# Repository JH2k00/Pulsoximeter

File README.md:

# Pulsoximeter
Pulsoximeter Projekt für den ETV

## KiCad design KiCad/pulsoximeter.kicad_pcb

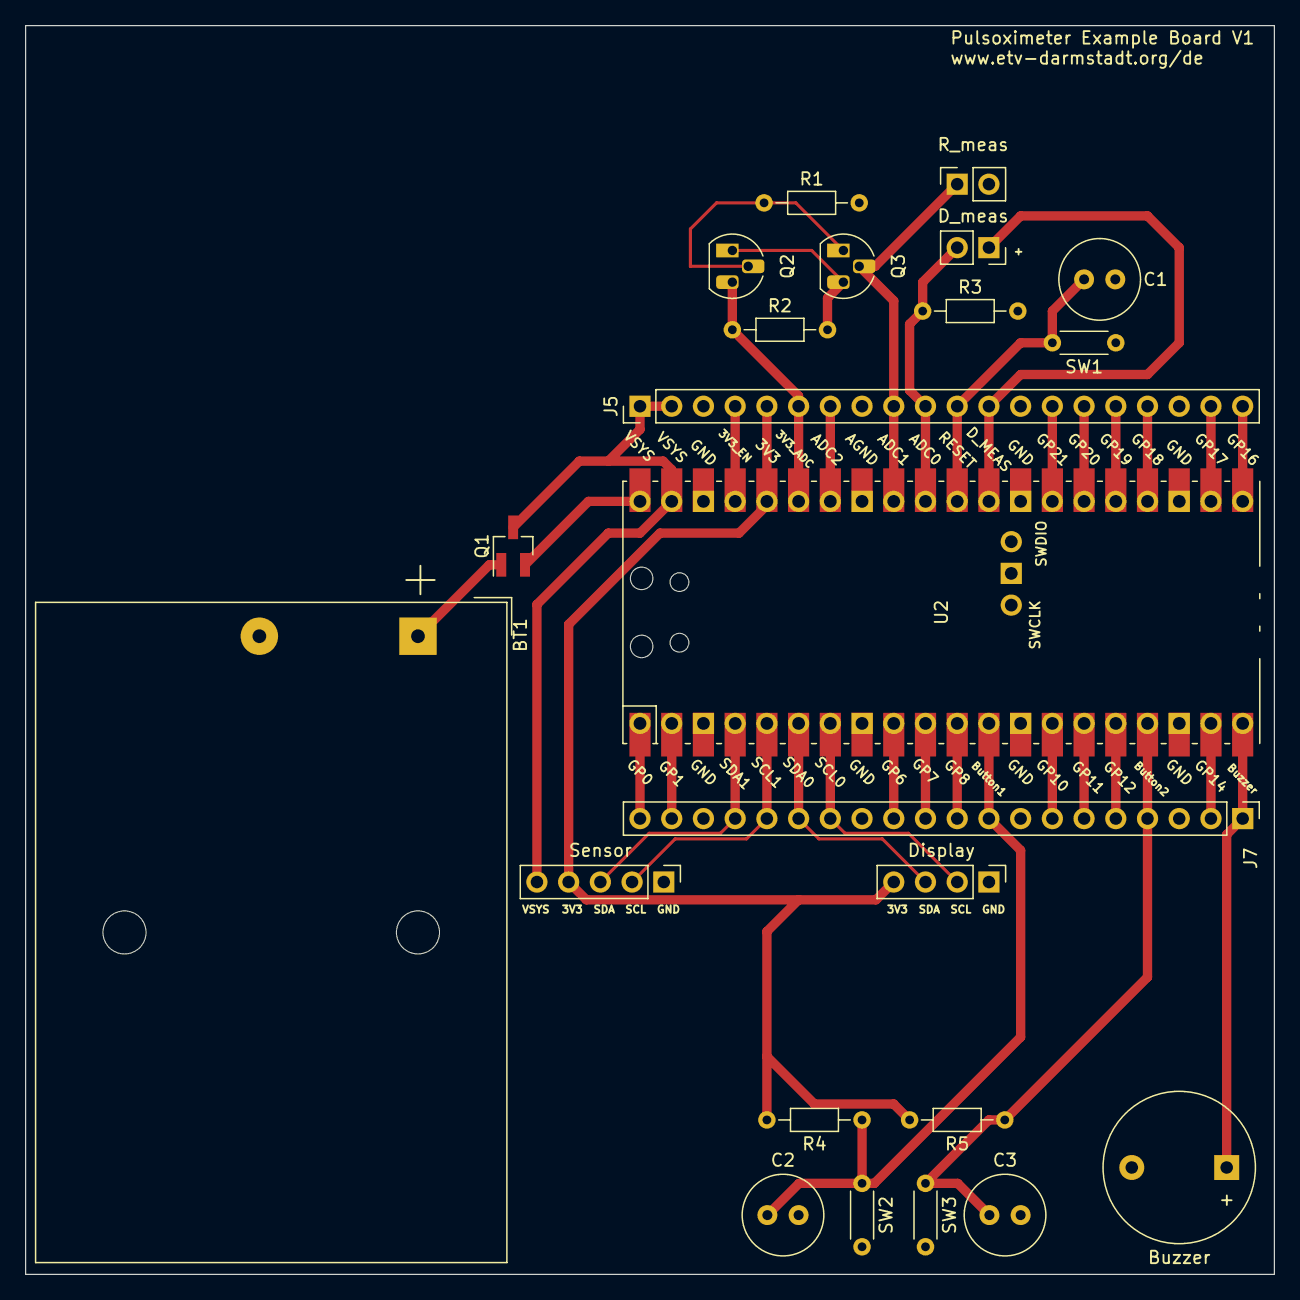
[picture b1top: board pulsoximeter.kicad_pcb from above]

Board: 2 copper layers, 100.0 x 100.0 mm, 23 parts (0 on the bottom side), 36 nets.

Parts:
BT1: Battery; BatteryHolder_Keystone_2479_3xAAA
Buzzer: Buzzer; Buzzer_12x9.5RM7.6
C1, C2, C3: 100n; C_Radial_D6.3mm_H5.0mm_P2.50mm
D_meas: D_meas; PinSocket_1x02_P2.54mm_Vertical
Display: Display Connector; PinHeader_1x04_P2.54mm_Vertical
J5: Analog; PinHeader_1x20_P2.54mm_Vertical
J7: Digital; PinHeader_1x20_P2.54mm_Vertical
Q1: DMG2305UX-13; SOT-23_Handsoldering
Q2, Q3: 2N3906C; TO-92_HandSolder
R1: 1Meg; R_Axial_DIN0204_L3.6mm_D1.6mm_P7.62mm_Horizontal
R2: 2k; R_Axial_DIN0204_L3.6mm_D1.6mm_P7.62mm_Horizontal
R3: 1k; R_Axial_DIN0204_L3.6mm_D1.6mm_P7.62mm_Horizontal
R4, R5: 10k; R_Axial_DIN0204_L3.6mm_D1.6mm_P7.62mm_Horizontal
R_meas: R_meas; PinSocket_1x02_P2.54mm_Vertical
SW1: SW_Push; R_Axial_DIN0204_L3.6mm_D1.6mm_P5.08mm_Horizontal
SW2: Display_Button; R_Axial_DIN0204_L3.6mm_D1.6mm_P5.08mm_Horizontal
SW3: Display_Button_2; R_Axial_DIN0204_L3.6mm_D1.6mm_P5.08mm_Horizontal
Sensor: MAX30102; PinHeader_1x05_P2.54mm_Vertical
U2: PicoW; RPi_PicoW_SMD_TH

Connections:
+3V3: Display.4, J5.5, R4.2, R5.2, Sensor.4, U2.36 (3V3)
+BATT: BT1.1 (+), Q1.1 (D)
/3V3_ADC: J5.6, Q2.3 (E), R2.1, U2.35 (ADC_VREF)
/3V3_EN: J5.4, U2.37 (3V3_EN)
/ADC0: D_meas.2, J5.10, R3.1, U2.31 (GPIO26_ADC0)
/ADC1: J5.9, Q3.2 (C), R_meas.1, U2.32 (GPIO27_ADC1)
/Buzzer: Buzzer.1 (-), J7.1, U2.20 (GPIO15)
/Diode_Meas: D_meas.1, J5.12, U2.29 (GPIO22)
/Display_Button1: C2.1, J7.9, R4.1, SW2.1, U2.12 (GPIO9)
/Display_Button2: C3.1, J7.4, R5.1, SW3.1, U2.17 (GPIO13)
/GP0: J7.20, U2.1 (GPIO0)
/GP1: J7.19, U2.2 (GPIO1)
/GP6: J7.12, U2.9 (GPIO6)
/GP7: J7.11, U2.10 (GPIO7)
/GP8: J7.10, U2.11 (GPIO8)
/GP10: J7.7, U2.14 (GPIO10)
/GP11: J7.6, U2.15 (GPIO11)
/GP12: J7.5, U2.16 (GPIO12)
/GP14: J7.2, U2.19 (GPIO14)
/GP16: J5.20, U2.21 (GPIO16)
/GP17: J5.19, U2.22 (GPIO17)
/GP18: J5.17, U2.24 (GPIO18)
/GP19: J5.16, U2.25 (GPIO19)
/GP20: J5.15, U2.26 (GPIO20)
/GP21: J5.14, U2.27 (GPIO21)
/GP28: J5.7, U2.34 (GPIO28_ADC2)
/I2C0 SCL: Display.2, J7.14, U2.7 (GPIO5)
/I2C0 SDA: Display.3, J7.15, U2.6 (GPIO4)
/I2C1 SCL: J7.16, Sensor.2, U2.5 (GPIO3)
/I2C1 SDA: J7.17, Sensor.3, U2.4 (GPIO2)
/RESET: C1.2, J5.11, SW1.2, U2.30 (RUN)
/VSYS: J5.1, J5.2, Q1.3 (S), Sensor.5, U2.39 (VSYS)
GND: BT1.2 (-), Buzzer.2 (+), C1.1, C2.2, C3.2, Display.1, J5.3, J5.8, J5.13, J5.18, J7.3, J7.8, J7.13, J7.18, R1.2, R3.2, R_meas.2, SW1.1, SW2.2, SW3.2, Sensor.1, U2.3 (GND), U2.8 (GND), U2.13 (GND), U2.18 (GND), U2.23 (GND), U2.28 (GND), U2.33 (AGND), U2.38 (GND)
unnamed: Q2.1 (B), Q3.3 (E), R2.2
unnamed: Q2.2 (C), Q3.1 (B), R1.1
VBUS: Q1.2 (G), U2.40 (VBUS)

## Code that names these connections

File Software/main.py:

from ulab import numpy as np
from machine import Pin, I2C, ADC, PWM
from MAX30102 import MAX30102, MAX3010X_I2C_ADDRESS, MAX30105_PULSEAMP_MEDIUM, MAX30105_PULSEAMP_LOW, I2C_SPEED_FAST, MAX30105_PULSEAMP_HIGH
import ssd1306
from utils import CONST_FIR_COEFFS
import struct
import asyncio
from utils import CONST_TONES, CONST_DEFAULT_SONG

from micropython import const

import aioble
import bluetooth

# org.bluetooth.service.pulse_oximeter
_PLX_SENSE_UUID = bluetooth.UUID(0x1822)

# org.bluetooth.characteristic.heart_rate_measurement
_PLX_CHAR_HR_UUID = bluetooth.UUID(0x2A37)

# org.bluetooth.characteristic.gap.appearance.xml
_ADV_APPEARANCE_GENERIC_PULSE_OXIMETER = const(0x0C40)

# How frequently to send advertising beacons.
_ADV_INTERVAL_MS = const(250000)

# Register GATT server.
plx_service = aioble.Service(_PLX_SENSE_UUID)
plx_characteristic = aioble.Characteristic(
    plx_service, _PLX_CHAR_HR_UUID, read=True, notify=True
)
aioble.register_services(plx_service)

I2C_0_SDA_PIN = Pin(4, pull=Pin.PULL_UP) # GPIO4 = Pin 6
I2C_0_SCL_PIN = Pin(5, pull=Pin.PULL_UP) # GPIO5 = Pin 7

I2C_1_SDA_PIN = Pin(2, pull=Pin.PULL_UP) # GPIO2 = Pin 4
I2C_1_SCL_PIN = Pin(3, pull=Pin.PULL_UP) # GPIO3 = Pin 5

adc1 = ADC(Pin(27, mode=Pin.IN))

gpio_pin = Pin(22, mode=Pin.OUT, value=1)
adc0 = ADC(Pin(26, mode=Pin.IN))

DISPLAY_STATE = 0 # 0 -> HR, 1-> Resistor, 2-> Diode

buzzer = PWM(Pin(15))
buzzer.freq(500)

def button_handler(pin):
    global DISPLAY_STATE
    DISPLAY_STATE = (DISPLAY_STATE + 1) % 3

button_2 = Pin(13, mode=Pin.IN)
button_2.irq(trigger=Pin.IRQ_FALLING, handler=button_handler)

I = 0.241751 # 0.241751 mA
U_LSB = (3.3) / (2**16) # U_ref = 3.3V, U_LSB = (U_ref / 2^n) V

LED = Pin('LED', Pin.OUT)
LED.toggle()

fs = 50 # Normal Heart rate is around 30-300 bpm -> f_max = 300 / 60 Hz = 5 Hz -> 50Hz sampling rate is more than enough

def i2c_print(devices):
        if len(devices) == 0:
            print("No i2c device !")
        else:
            print('i2c devices found:',len(devices))

        for device in devices:
            print("Decimal address: ",device," | Hexa address: ",hex(device))

i2c_0 = I2C(0, sda=I2C_0_SDA_PIN, scl=I2C_0_SCL_PIN, freq=I2C_SPEED_FAST)
i2c_print(devices=i2c_0.scan())

i2c_1 = I2C(1, sda=I2C_1_SDA_PIN, scl=I2C_1_SCL_PIN, freq=I2C_SPEED_FAST)
i2c_print(devices=i2c_1.scan())

display = ssd1306.SSD1306_I2C(128, 32, i2c_0)

display.fill(0) # Clear previous text
display.text('Collecting', 0, 10, 1)
display.text('samples ...', 0, 20 , 1)
display.show()

sensor = MAX30102(MAX3010X_I2C_ADDRESS, i2c_1)
sensor.setup_sensor(LED_POWER=MAX30105_PULSEAMP_MEDIUM)
sensor.clearFIFO()
sensor.setSampleRate(fs)
sensor.setFIFOAverage(1)

# Helper to encode the heart rate characteristic encoding (uint16).
def _encode_heart_rate(hr):
    return struct.pack(">h", int(hr))

# This would be periodically polling a hardware sensor.
async def read_heart_rate():
    red = []
    #ir = []

    n_readings = 512 # Must be a power of 2
    n_overlap = int(0.95*n_readings)

    freq_resolution = float(fs) / float(n_readings)
    N = n_readings//2 + 1
    f = np.array(list(range(N)))*freq_resolution*60 # Frequency vector in bpm
    f_min = 30 # Minimal heart rate frequency in bpm
    f_max = 200 # Maximal heart rate frequency in bpm

    # Smoothing
    periodogram_smooth = np.zeros(f.shape)
    forgetting_factor = 0.9
    first_update = True # Flag for the first update in order to ignore forgetting factor

    heart_rate = 0

    while True:
        sensor.check()
        # Check if the storage contains available samples
        if(sensor.available()):
            # Access the storage FIFO and gather the readings (integers)
            red_reading = sensor.popRedFromStorage()
            IR_reading = sensor.popIRFromStorage()
            red.append(red_reading)
            #ir.append(IR_reading)
            n = len(red)
            if(n >= n_readings):
                red_np = np.array(red) - np.mean(red)
                real, imag = np.fft.fft(red_np)
                real = real[:N]
                imag = imag[:N]
                periodogram = (real*real + imag*imag)
                periodogram[f < f_min] = 0 # Set periodogram of frequencies outside the range to 0
                periodogram[f > f_max] = 0 # Set periodogram of frequencies outside the range to 0
                if(first_update):
                    periodogram_smooth = periodogram
                    first_update = False
                else:
                    periodogram_smooth = forgetting_factor * periodogram_smooth + (1-forgetting_factor) * periodogram # Update current periodogram estimate with the smoothing equation
                heart_rate = f[np.argmax(periodogram_smooth)]
                print(heart_rate)
                if(DISPLAY_STATE == 0):
                    display.fill(0) # Clear previous text
                    display.text('HR : %.3f' %heart_rate, 0, 10, 1)
                    display.show()
                red = red[-n_overlap:]
        plx_characteristic.write(_encode_heart_rate(heart_rate)) # Update Bluetooth
        await asyncio.sleep_ms(int(1000 / (2*fs)))

# Serially wait for connections. Don't advertise while a central is
# connected.
async def peripheral_task():
    while True:
        async with await aioble.advertise(
            _ADV_INTERVAL_MS,
            name="etv-pulse-oximeter",
            services=[_PLX_SENSE_UUID],
            appearance=_ADV_APPEARANCE_GENERIC_PULSE_OXIMETER,
        ) as connection:
            print("Connection from", connection.device)
            await connection.disconnected()

async def measure_diode():
    while True:
        V = float(adc0.read_u16()) * U_LSB
        V_diode = 3.3 - V 
        if(DISPLAY_STATE == 2):
            display.fill(0) # Clear previous text
            display.text('V_d = %.3f V' %V_diode, 0, 10, 1)
            display.show()
        await asyncio.sleep_ms(500)
    #print("Diode Forward Voltage is V = %.3f V" %(V_diode))

async def measure_resistor():
    while True:
        V = float(adc1.read_u16()) * U_LSB
        R = V / I; # R in kOhm
        if(DISPLAY_STATE == 1):
            display.fill(0)# Clear previous text
            if(R < 1):
                display.text('R = %.3f Ohm' %(R*1000), 0, 10, 1)
            else:
                display.text('R = %.3f kOhm' %R, 0, 10, 1)
            display.show()
        await asyncio.sleep_ms(500)

# Run both tasks.
async def main():
    t1 = asyncio.create_task(read_heart_rate())
    t2 = asyncio.create_task(peripheral_task())
    t3 = asyncio.create_task(measure_resistor())
    t4 = asyncio.create_task(measure_diode())
    await asyncio.gather(t1, t2, t3, t4, return_exceptions=True)

asyncio.run(main())

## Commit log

2023-08-23 Reordered files, and first steps in Schematic
2023-09-08 Finished schematic and footprint assignment
2023-09-13 PCB Design V1 is mostly done. Still have to add some cool art
2023-09-14 Added cool logos to the PCB and generated Gerbers
2023-09-30 Started Software Development and stored away old software
2023-09-30 Started working on a new software
2023-09-30 Old commits from pcb design
2023-10-02 Designed Bandpass Filter in MATLAB
2023-10-02 Started working on bluetooth
2023-10-11 Updated Pico Software and Firmware. Also added a script in order to show ppg data
2023-10-16 Added a bluetooth test script for PC
2023-10-16 Fixed serialPlotter
2023-10-16 Updated ble script. We can now receive data from the pico w over bluetooth on the PC
2023-10-17 Added plot function to BLE Client on PC
